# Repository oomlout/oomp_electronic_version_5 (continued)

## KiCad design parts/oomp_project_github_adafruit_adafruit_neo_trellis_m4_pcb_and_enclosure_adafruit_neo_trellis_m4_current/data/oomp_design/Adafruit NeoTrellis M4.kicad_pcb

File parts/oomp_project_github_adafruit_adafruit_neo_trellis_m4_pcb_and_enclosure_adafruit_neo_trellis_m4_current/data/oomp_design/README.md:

# OOMP KiCad design copy

Open `Adafruit NeoTrellis M4.kicad_pro` (or the `.kicad_pcb` / `.kicad_sch`) in KiCad. Local OOMP libraries are under `libraries/`. Original inputs are preserved in [../original/](../original/).

Only verified unchanged installed KiCad defaults were renamed. Modified, custom, unmatched and unavailable items remain unchanged. Soldering variants are never swapped during conversion. Existing pad coordinates, nets and UUIDs are preserved.

See [conversion_report.yaml](conversion_report.yaml) for every conversion and skip. Copy this directory before editing; regeneration refuses to overwrite edited design files.

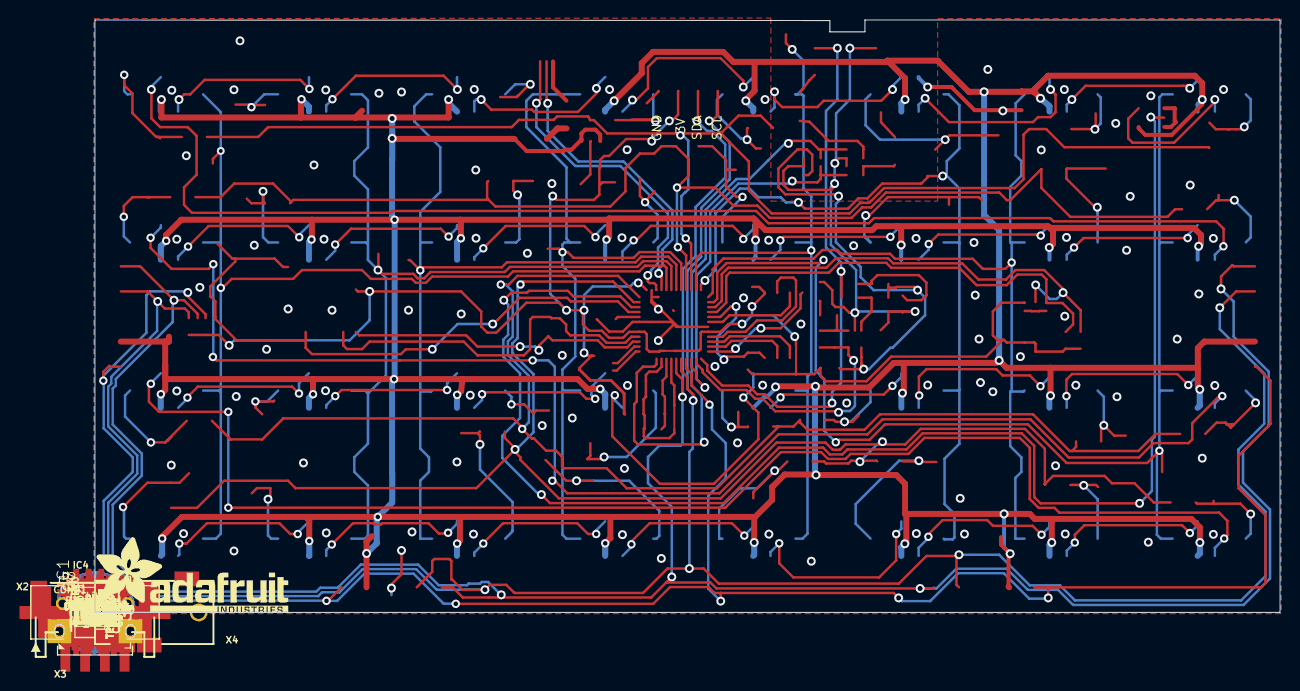
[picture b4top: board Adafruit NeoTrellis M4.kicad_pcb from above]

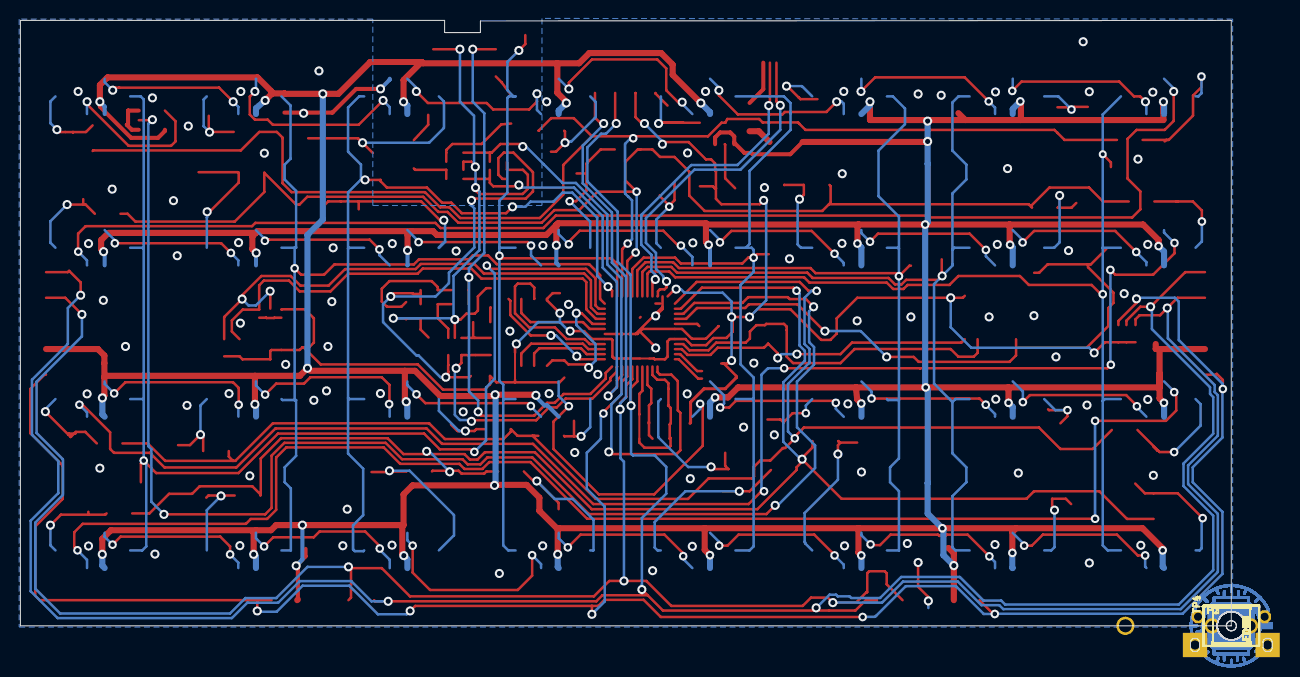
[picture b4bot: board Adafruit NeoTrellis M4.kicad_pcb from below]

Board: 2 copper layers, 124.1 x 62.6 mm, 228 parts (71 on the bottom side), 117 nets.

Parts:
C1, C2, C3, C4, C5, C6: 10u; 0805-NO
C7, C8: 100uF; C1210
C9, C11: 10µF; 0805-NO
C10, C12, C14, C21, C22: 1uF; 0603-NO
C13, C19, C20: 10uF; 0805-NO
C15, C23: 0.1uF; 0603-NO
C16: 0.1µF; 0603-NO
C17: 0.01uF; 0603-NO
C18: 100pF; 0603-NO
CONN1: STEMMA_I2C_RASMT; JSTPH4
D1, D2, D3, D4, D5, D6, D7, D8, D9, D10, D11, D12, D13, D14, D15, D16, D17, D18, D19, D20, D21, D22, D23, D24, D25, D26, D27, D28, D29, D30, D31, D32: 1N4148; SOD-323
D34: MBR120; SOD-123FL
FB1, FB2: FERRITE; 0805
FB3, FB4: FERRITE; 0805-NO
FID1, FID2, FID3, FID4, FID5, FID6: FIDUCIAL_1MM
IC1: 74HCT1G125DBV; SOT23-5
IC4: ATSAMD51G_TQFN48; TQFN48_7MM
JP1, JP2, JP3, JP4: 5P_EDGECONNECT
L2: AP102-2020; APA102_2020
LED1, LED2, LED3, LED4, LED5, LED6, LED7, LED8, LED9, LED10, LED11, LED12, LED13, LED14, LED15, LED16, LED17, LED18, LED19, LED20, LED21, LED22, LED23, LED24, LED25, LED26, LED27, LED28, LED29, LED30, LED31, LED32: WS2812B3535; LED3535
PTC1: 500mA Fuse; 1206
R1, R2: 10K; RESPACK_4X0603
R3, R4, R5: 1K; 0603-NO
R6, R7: 1M; 0603-NO
R8: 100K; 0603-NO
R9, R11, R12, R13: 10K; 0603-NO
R10: 100; RESPACK_4X0603
SW1: SPST_TACT-KMR2; KMR2
TP1, TP2, TP3, TP4: TESTPOINT_SMT
TP5, TP6: TESTPOINT_ROUND_2MM
TP7, TP8, TP12, TP13, TP14, TP15, TP16, TP17, TP18, TP19, TP20, TP21, TP22, TP23, TP24, TP25, TP26, TP27, TP28, TP29, TP30, TP31, TP32, TP33, TP34, TP35, TP36, TP37, TP38, TP39, TP40, TP41, TP42, TP43, TP44, TP45, TP46, TP47, TP48, TP49, TP50: TESTPOINT_ROUND_1.5MM
U1: AP2112K-3.3; SOT23-5
U2: MAX4466EXK+T; SC70-5
U3: GD25x16; SOIC8_208MIL
U4: LGA14
U$3: ADAFRUIT_TEXT_20MM
U$4, U$5, U$6, U$7, U$8, U$9, U$10, U$11, U$12, U$19, U$23, U$24, U$25, U$26, U$27, U$28, U$29, U$33, U$34, U$35, U$36, U$37, U$38, U$39, U$40, U$41, U$42, U$43, U$44, U$45, U$46, U$47: ELAST_10X10; ELAST_PAD_SQUARE_10MM_4X4WIDE
U$48: TRELLISLOGO
U$78: PCBFEAT-REV-040
UNK_HOLE_0: dummyfp0
UNK_HOLE_1: dummyfp1
UNK_HOLE_2: dummyfp2
UNK_HOLE_3: dummyfp3
UNK_HOLE_4: dummyfp4
UNK_HOLE_5: dummyfp5
UNK_HOLE_6: dummyfp6
UNK_HOLE_7: dummyfp7
UNK_HOLE_8: dummyfp8
UNK_HOLE_9: dummyfp9
UNK_HOLE_10: dummyfp10
UNK_HOLE_11: dummyfp11
UNK_HOLE_12: dummyfp12
UNK_HOLE_13: dummyfp13
UNK_HOLE_14: dummyfp14
UNK_HOLE_15: dummyfp15
UNK_HOLE_16: dummyfp16
UNK_HOLE_17: dummyfp17
X2: 2x5 0.05" SWD; 2X05_1.27MM_BOX_POSTS
X3: microUSB; 4UCONN_20329_NARROW
X4: 4UCONN_18510

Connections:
3.3V: C10.1, C11.1, C12.1, C14.1, C23.1, CONN1.2, FB2.2, FB3.1, IC4.17, IC4.36, IC4.44, L2.3, R2.5, R2.6, R2.7, R2.8, R9.1, R11.2, R12.1, R13.1, U1.5, U3.8, U4.1, U4.6, U4.7, X2.1
A0: IC4.3, R1.3, R1.4, R10.5
A1: IC4.10, R1.1, R1.2, R10.8
AGND: C16.2, C19.2, FB1.2, R1.6, R1.7, R6.1, R10.6, R10.7, U2.2, X4.4-INNER_SLEEVE
AVCC: FB2.1, R1.5, R1.8, R4.2, R7.2, U2.5
AVDD: C20.1, C21.1, C22.1, FB3.2, IC4.4, IC4.6
COL0: IC4.23, TP12.P$1, U$4.P$1, U$8.P$1, U$12.P$1, U$26.P$1
COL1: IC4.24, TP13.P$1, U$5.P$1, U$9.P$1, U$23.P$1, U$27.P$1
COL2: IC4.25, TP14.P$1, U$6.P$1, U$10.P$1, U$25.P$1, U$28.P$1
COL3: IC4.26, TP15.P$1, U$7.P$1, U$11.P$1, U$24.P$1, U$29.P$1
COL4: IC4.29, TP16.P$1, U$19.P$1, U$36.P$1, U$40.P$1, U$44.P$1
COL5: IC4.30, TP17.P$1, U$33.P$1, U$37.P$1, U$41.P$1, U$45.P$1
COL6: IC4.31, TP18.P$1, U$34.P$1, U$38.P$1, U$43.P$1, U$46.P$1
COL7: IC4.32, TP19.P$1, U$35.P$1, U$39.P$1, U$42.P$1, U$47.P$1
D+: IC4.34, X3.D+
D-: IC4.33, X3.D-
DOTSTAR_CLK: IC4.47, L2.5
DOTSTAR_DATA: IC4.48, L2.6
GND: C1.1, C2.1, C3.1, C4.1, C5.1, C6.1, C9.2, C10.2, C11.2, C12.2, C13.2, C14.2, C15.1, C23.2, CONN1.1, FB1.1, FB4.1, IC1.1, IC1.3, IC4.18, IC4.35, IC4.42, IC4.THERMAL, JP1.3, JP2.3, JP3.3, JP4.3, L2.4, LED1.4, LED2.4, LED3.4, LED4.4, LED5.4, LED6.4, LED7.4, LED8.4, LED9.4, LED10.4, LED11.4, LED12.4, LED13.4, LED14.4, LED15.4, LED16.4, LED17.4, LED18.4, LED19.4, LED20.4, LED21.4, LED22.4, LED23.4, LED24.4, LED25.4, LED26.4, LED27.4, LED28.4, LED29.4, LED30.4, LED31.4, LED32.4, SW1.2, SW1.4, TP1.P$1, TP2.P$1, TP3.P$1, TP4.P$1, U1.2, U3.4, U4.2, U4.4, U4.5, U4.12, X2.3, X2.5, X3.BASE@1, X3.BASE@2, X3.GND, X3.SPRT@1, X3.SPRT@2, X3.SPRT@3, X3.SPRT@4
INT: IC4.9, JP1.1, JP2.1, JP3.1, JP4.1, R2.2
LEFT: C7.2, X4.2-TIP
MIC_IN: C17.1, IC4.12, R3.1, X4.1-GND
MIC_OUT: C18.1, IC4.11, R8.2, U2.4
unnamed: C8.1, R10.3, R10.4
unnamed: D9.C, TP20.P$1, U$4.P$2
unnamed: D1.C, TP21.P$1, U$5.P$2
unnamed: D2.C, TP22.P$1, U$6.P$2
unnamed: D3.C, TP23.P$1, U$7.P$2
unnamed: D4.C, TP8.P$1, U$8.P$2
unnamed: LED17.3, LED18.1
unnamed: LED18.3, LED19.1
unnamed: D5.C, TP24.P$1, U$9.P$2
unnamed: LED19.3, LED20.1
unnamed: LED1.3, LED2.1
unnamed: LED2.3, LED3.1
unnamed: LED3.3, LED4.1
unnamed: LED4.3, LED5.1
unnamed: D6.C, TP34.P$1, U$10.P$2
unnamed: LED5.3, LED6.1
unnamed: LED6.3, LED7.1
unnamed: D7.C, TP25.P$1, U$11.P$2
unnamed: LED7.3, LED8.1
unnamed: D8.C, TP33.P$1, U$12.P$2
unnamed: LED8.3, LED9.1
unnamed: D10.C, TP26.P$1, U$23.P$2
unnamed: D11.C, TP32.P$1, U$25.P$2
unnamed: D12.C, TP27.P$1, U$24.P$2
unnamed: D13.C, TP31.P$1, U$26.P$2
unnamed: D14.C, TP28.P$1, U$27.P$2
unnamed: D15.C, TP30.P$1, U$28.P$2
unnamed: D16.C, TP29.P$1, U$29.P$2
unnamed: LED9.3, LED10.1
unnamed: LED10.3, LED12.1
unnamed: LED11.1, LED12.3
unnamed: LED11.3, LED13.1
unnamed: LED13.3, LED14.1
unnamed: LED14.3, LED15.1
unnamed: LED15.3, LED16.1
unnamed: LED20.3, LED21.1
unnamed: LED21.3, LED22.1
unnamed: LED22.3, LED23.1
unnamed: LED23.3, LED24.1
unnamed: LED24.3, LED25.1
unnamed: LED25.3, LED26.1
unnamed: LED26.3, LED28.1
unnamed: LED27.1, LED28.3
unnamed: LED27.3, LED29.1
unnamed: LED29.3, LED30.1
unnamed: LED30.3, LED31.1
unnamed: LED31.3, LED32.1
unnamed: D17.C, TP35.P$1, U$19.P$2
unnamed: D18.C, TP36.P$1, U$33.P$2
unnamed: D19.C, TP38.P$1, U$34.P$2
unnamed: D20.C, TP37.P$1, U$35.P$2
unnamed: D21.C, TP39.P$1, U$36.P$2
unnamed: D22.C, TP40.P$1, U$37.P$2
unnamed: D23.C, TP42.P$1, U$38.P$2
unnamed: D24.C, TP41.P$1, U$39.P$2
unnamed: D25.C, TP43.P$1, U$40.P$2
unnamed: D26.C, TP44.P$1, U$41.P$2
unnamed: D27.C, TP46.P$1, U$43.P$2
unnamed: D28.C, TP45.P$1, U$42.P$2
unnamed: D29.C, TP47.P$1, U$44.P$2
unnamed: D30.C, TP49.P$1, U$45.P$2
unnamed: D31.C, TP48.P$1, U$46.P$2
unnamed: D32.C, TP50.P$1, U$47.P$2
unnamed: LED16.3, LED17.1
unnamed: C16.1, R3.2, R4.1
unnamed: PTC1.2, X3.VBUS
unnamed: C17.2, R6.2, R7.1, U2.1
unnamed: C18.2, R5.1, R8.1, U2.3
unnamed: C19.1, R5.2
unnamed: C7.1, R10.1, R10.2
NEOPIXEL_3V: IC1.2, IC4.39
NEOPIXEL_5V: IC1.4, LED1.1
QSPI_CS: IC4.20, R9.2, U3.1
QSPI_DATA[0]: IC4.13, U3.5
QSPI_DATA[1]: IC4.14, U3.2
QSPI_DATA[2]: IC4.15, U3.3
QSPI_DATA[3]: IC4.16, U3.7
QSPI_SCK: IC4.19, U3.6
RIGHT: C8.2, X4.3-OUTER_SLEEVE
ROW0: D1.A, D2.A, D3.A, D9.A, D17.A, D18.A, D19.A, D20.A, IC4.27
ROW1: D4.A, D5.A, D6.A, D7.A, D21.A, D22.A, D23.A, D24.A, IC4.28
ROW2: D8.A, D10.A, D11.A, D12.A, D25.A, D26.A, D27.A, D28.A, IC4.37
ROW3: D13.A, D14.A, D15.A, D16.A, D29.A, D30.A, D31.A, D32.A, IC4.38
SCL: CONN1.4, IC4.8, JP1.4, JP2.4, JP3.4, JP4.4, R2.4
SCL1: IC4.22, R13.2, U4.14
SDA: CONN1.3, IC4.7, JP1.5, JP2.5, JP3.5, JP4.5, R2.3
SDA1: IC4.21, R12.2, U4.13
SWCLK: IC4.45, R11.1, TP5.P$1, X2.4
SWDIO: IC4.46, TP6.P$1, X2.2
VBUS: D34.A, PTC1.1
VDD: C1.2, C2.2, C3.2, C4.2, C5.2, C6.2, C9.1, D34.C, IC1.5, JP1.2, JP2.2, JP3.2, JP4.2, LED1.2, LED2.2, LED3.2, LED4.2, LED5.2, LED6.2, LED7.2, LED8.2, LED9.2, LED10.2, LED11.2, LED12.2, LED13.2, LED14.2, LED15.2, LED16.2, LED17.2, LED18.2, LED19.2, LED20.2, LED21.2, LED22.2, LED23.2, LED24.2, LED25.2, LED26.2, LED27.2, LED28.2, LED29.2, LED30.2, LED31.2, LED32.2, U1.1, U1.3
VDDCORE: C13.1, IC4.41
VSS: C20.2, C21.2, C22.2, FB4.2, IC4.5
~RESET: C15.2, IC4.40, R2.1, SW1.1, SW1.3, TP7.P$1, X2.10

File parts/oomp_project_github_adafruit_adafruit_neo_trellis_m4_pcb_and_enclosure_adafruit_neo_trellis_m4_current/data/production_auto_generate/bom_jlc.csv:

Comment,Designator,Footprint,LCSC Part #
,"JP1,JP2,JP3,JP4",Adafruit NeoTrellis M4-import-fps:5P_EDGECONNECT,
,U$3,Adafruit NeoTrellis M4-import-fps:ADAFRUIT_TEXT_20MM,
,U4,Adafruit NeoTrellis M4-import-fps:LGA14,
,U$78,Adafruit NeoTrellis M4-import-fps:PCBFEAT-REV-040,
,"TP7,TP8,TP12,TP13,TP14,TP15,TP16,TP17,TP18,TP19,TP20,TP21,TP22,TP23,TP24,TP25,TP26,TP27,TP28,TP29,TP30,TP31,TP32,TP33,TP34,TP35,TP36,TP37,TP38,TP39,TP40,TP41,TP42,TP43,TP44,TP45,TP46,TP47,TP48,TP49,TP50",Adafruit NeoTrellis M4-import-fps:TESTPOINT_ROUND_1.5MM,
,"TP5,TP6",Adafruit NeoTrellis M4-import-fps:TESTPOINT_ROUND_2MM,
,"TP1,TP2,TP3,TP4",Adafruit NeoTrellis M4-import-fps:TESTPOINT_SMT,
,U$48,Adafruit NeoTrellis M4-import-fps:TRELLISLOGO,
0.01uF,C17,Adafruit NeoTrellis M4-import-fps:0603-NO,C5137477
0.1uF,"C15,C23",Adafruit NeoTrellis M4-import-fps:0603-NO,C14663
0.1µF,C16,Adafruit NeoTrellis M4-import-fps:0603-NO,C14663
100,R10,Adafruit NeoTrellis M4-import-fps:RESPACK_4X0603,C22775
100K,R8,Adafruit NeoTrellis M4-import-fps:0603-NO,C25803
100pF,C18,Adafruit NeoTrellis M4-import-fps:0603-NO,
100uF,"C7,C8",Adafruit NeoTrellis M4-import-fps:C1210,
10K,"R9,R11,R12,R13",Adafruit NeoTrellis M4-import-fps:0603-NO,C98220
10K,"R1,R2",Adafruit NeoTrellis M4-import-fps:RESPACK_4X0603,C98220
10u,"C1,C2,C3,C4,C5,C6",Adafruit NeoTrellis M4-import-fps:0805-NO,
10uF,"C13,C19,C20",Adafruit NeoTrellis M4-import-fps:0805-NO,
10µF,"C9,C11",Adafruit NeoTrellis M4-import-fps:0805-NO,
1K,"R3,R4,R5",Adafruit NeoTrellis M4-import-fps:0603-NO,C2907002
1M,"R6,R7",Adafruit NeoTrellis M4-import-fps:0603-NO,C2907003
1N4148,"D1,D2,D3,D4,D5,D6,D7,D8,D9,D10,D11,D12,D13,D14,D15,D16,D17,D18,D19,D20,D21,D22,D23,D24,D25,D26,D27,D28,D29,D30,D31,D32",Adafruit NeoTrellis M4-import-fps:SOD-323,
1uF,"C10,C12,C14,C21,C22",Adafruit NeoTrellis M4-import-fps:0603-NO,C5673
"2x5 0.05"" SWD",X2,Adafruit NeoTrellis M4-import-fps:2X05_1.27MM_BOX_POSTS,
4UCONN_18510,X4,Adafruit NeoTrellis M4-import-fps:4UCONN_18510,
500mA Fuse,PTC1,Adafruit NeoTrellis M4-import-fps:1206,
74HCT1G125DBV,IC1,Adafruit NeoTrellis M4-import-fps:SOT23-5,
AP102-2020,L2,Adafruit NeoTrellis M4-import-fps:APA102_2020,
AP2112K-3.3,U1,Adafruit NeoTrellis M4-import-fps:SOT23-5,
ATSAMD51G_TQFN48,IC4,Adafruit NeoTrellis M4-import-fps:TQFN48_7MM,
ELAST_10X10,"U$4,U$5,U$6,U$7,U$8,U$9,U$10,U$11,U$12,U$19,U$23,U$24,U$25,U$26,U$27,U$28,U$29,U$33,U$34,U$35,U$36,U$37,U$38,U$39,U$40,U$41,U$42,U$43,U$44,U$45,U$46,U$47",Adafruit NeoTrellis M4-import-fps:ELAST_PAD_SQUARE_10MM_4X4WIDE,
FERRITE,"FB1,FB2",Adafruit NeoTrellis M4-import-fps:0805,
FERRITE,"FB3,FB4",Adafruit NeoTrellis M4-import-fps:0805-NO,
GD25x16,U3,Adafruit NeoTrellis M4-import-fps:SOIC8_208MIL,
MAX4466EXK+T,U2,Adafruit NeoTrellis M4-import-fps:SC70-5,
MBR120,D34,Adafruit NeoTrellis M4-import-fps:SOD-123FL,
microUSB,X3,Adafruit NeoTrellis M4-import-fps:4UCONN_20329_NARROW,
SPST_TACT-KMR2,SW1,Adafruit NeoTrellis M4-import-fps:KMR2,
STEMMA_I2C_RASMT,CONN1,Adafruit NeoTrellis M4-import-fps:JSTPH4,
WS2812B3535,"LED1,LED2,LED3,LED4,LED5,LED6,LED7,LED8,LED9,LED10,LED11,LED12,LED13,LED14,LED15,LED16,LED17,LED18,LED19,LED20,LED21,LED22,LED23,LED24,LED25,LED26,LED27,LED28,LED29,LED30,LED31,LED32",Adafruit NeoTrellis M4-import-fps:LED3535,
